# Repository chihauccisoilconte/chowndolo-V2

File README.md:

# chowndolo-V2

The present repository contains the documentation relative to the redesign of the "Chowndolo" project by Giacomo Lepri (http://www.giacomolepri.com/chowndolo).

This project it has been developed in 2022/23 as part of the research project entitled "Redesigning the Chowndolo: a Reflection-on-action Analysis to Identify Sustainable Strategies for NIMEs Design", conducted by Nicolò Merendino, Giacomo Lepri, and Raul Masu.

The repository contains CAD files, circuit schematics, and research materials produced in the project's development.

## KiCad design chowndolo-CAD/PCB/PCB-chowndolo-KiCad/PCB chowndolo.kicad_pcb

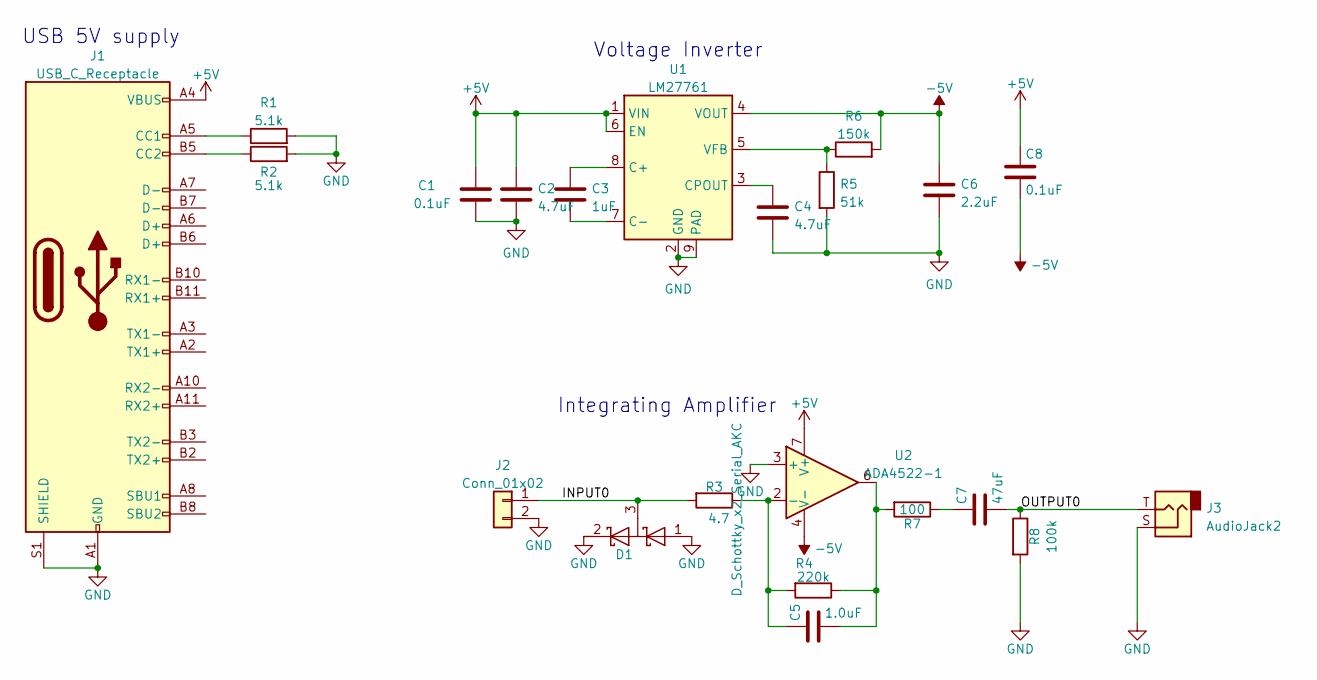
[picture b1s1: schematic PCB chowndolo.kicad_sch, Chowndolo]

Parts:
C1, C8: 0.1uF; C_0603_1608Metric
C2, C4: 4.7uF; C_0603_1608Metric
C3: 1uF; C_0603_1608Metric
C5: 1.0uF; C_0603_1608Metric
C6: 2.2uF; C_0603_1608Metric
C7: 47uF; C_1206_3216Metric
D1: D_Schottky_x2_Serial_AKC; SOT-23
J1: USB_C_Receptacle; USB_C_Receptacle_Amphenol_12401610E4-2A
J2: Conn_01x02; Molex_KK-254_AE-6410-02A_1x02_P2.54mm_Vertical
J3: AudioJack2; Jack_3.5mm_CUI_SJ1-3533NG_Horizontal
R1, R2: 5.1k; R_0603_1608Metric
R3: 4.7; R_0603_1608Metric
R4: 220k; R_0603_1608Metric
R5: 51k; R_0603_1608Metric
R6: 150k; R_0603_1608Metric
R7: 100; R_0603_1608Metric
R8: 100k; R_0603_1608Metric
U1: LM27761; WSON-8-1EP_2x2mm_P0.5mm_EP0.9x1.6mm
U2: ADA4522-1; MSOP-8_3x3mm_P0.65mm

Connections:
+5V: C1.1, C2.1, C8.1, J1.A4 (VBUS), J1.A9 (VBUS), J1.B4 (VBUS), J1.B9 (VBUS), U1.1 (VIN), U1.6 (EN), U2.7 (V+)
-5V: C6.1, C8.2, R6.2, U1.4 (VOUT), U2.4 (V-)
/INPUT0: D1.3 (common), J2.1, R3.2
/OUTPUT0: C7.2, J3.T, R8.1
GND: C1.2, C2.2, C4.2, C6.2, D1.1 (A), D1.2 (K), J1.A1 (GND), J1.A12 (GND), J1.B1 (GND), J1.B12 (GND), J1.S1 (SHIELD), J2.2, J3.S, R1.2, R2.2, R5.2, R8.2, U1.2 (GND), U1.9 (PAD), U2.3 (+)
unnamed: C3.1, U1.8 (C+)
unnamed: C3.2, U1.7 (C-)
unnamed: C4.1, U1.3 (CPOUT)
unnamed: C5.1, R3.1, R4.2, U2.2 (-)
unnamed: C5.2, R4.1, R7.2, U2.6
unnamed: C7.1, R7.1
unnamed: J1.A5 (CC1), R1.1
unnamed: J1.B5 (CC2), R2.1
unnamed: R5.1, R6.1, U1.5 (VFB)

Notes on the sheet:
Integrating Amplifier
USB 5V supply
Voltage Inverter

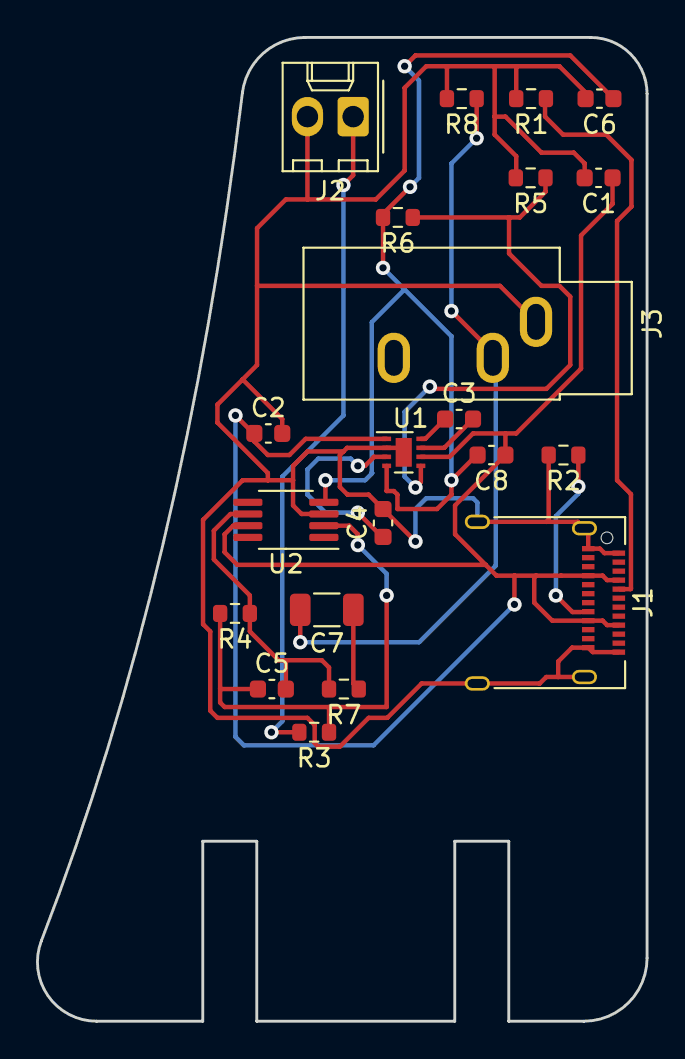
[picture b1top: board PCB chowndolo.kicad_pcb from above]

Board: 2 copper layers, 33.9 x 54.7 mm, 21 parts (0 on the bottom side), 14 nets.
